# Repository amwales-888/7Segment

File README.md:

# 7Segment
Simple Large 7Segment Display

Who doesn't love big 7Segment displays?
Modelled the hardware in solidworks, printed on BambuLabs P1S. PCBs designed in KiCAD and boards manufactured by JLPCB.
The microcontroller I am using is a dsPIC33CK and it is interfaced to the WS2812 chips through DMA->SPI. It took quite a bit of fiddling to get the DMA->SPI working. 
</p>
For the clock I used a battery backed ds3102, 3 button's allow you to set the time and change the colors.
</p>
<table>
  <tr>
    <td> </td>
    <td> </td>
  </tr>
  <tr>
    <td> </td>
    <td> </td>
  </tr>
  <tr>
    <td> </td>
    <td> </td>
  </tr>
</table>

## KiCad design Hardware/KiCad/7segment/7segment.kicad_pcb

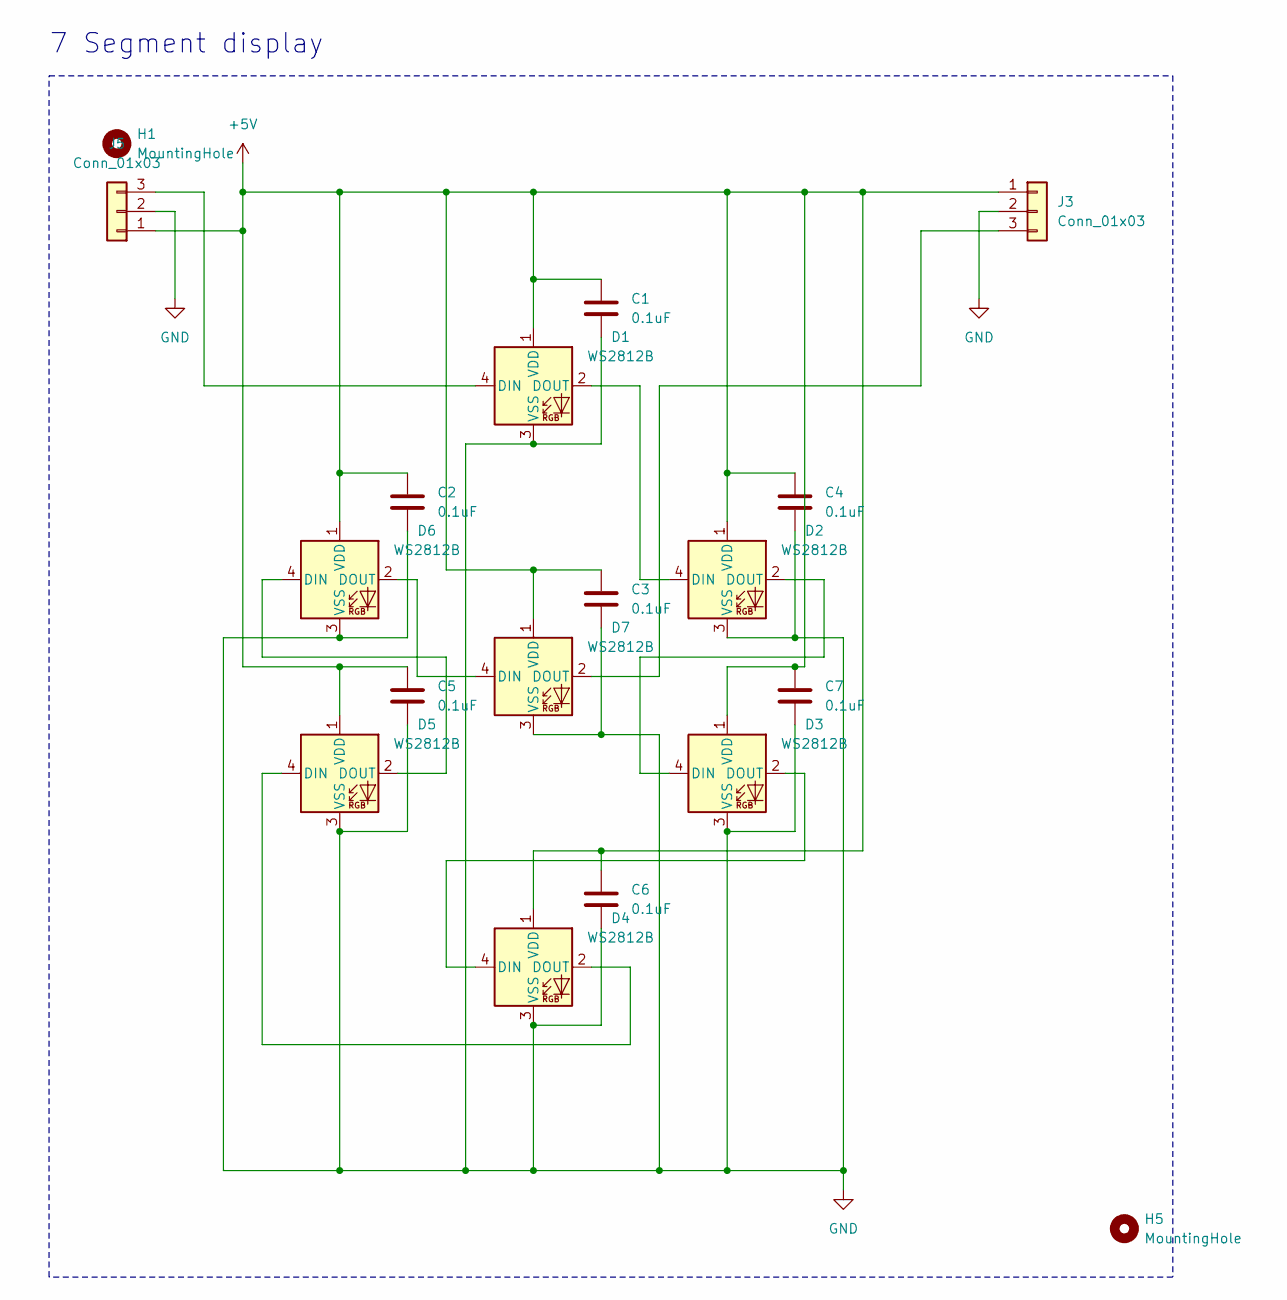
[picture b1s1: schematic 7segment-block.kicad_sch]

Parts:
C1, C2, C3, C4, C5, C6, C7: 0.1uF; C_0805_2012Metric_Pad1.18x1.45mm_HandSolder
D1, D2, D3, D4, D5, D6, D7: WS2812B; LED_WS2812B_PLCC4_5.0x5.0mm_P3.2mm
H1, H5: MountingHole; MountingHole_3.2mm_M3
J3, J5: Conn_01x03; PinHeader_1x03_P2.54mm_Vertical

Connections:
+5V: C1.1, C2.1, C3.1, C4.1, C5.1, C6.1, C7.1, D1.1 (VDD), D2.1 (VDD), D3.1 (VDD), D4.1 (VDD), D5.1 (VDD), D6.1 (VDD), D7.1 (VDD), J3.1, J5.1
GND: C1.2, C2.2, C3.2, C4.2, C5.2, C6.2, C7.2, D1.3 (VSS), D2.3 (VSS), D3.3 (VSS), D4.3 (VSS), D5.3 (VSS), D6.3 (VSS), D7.3 (VSS), J3.2, J5.2
unnamed: D1.4 (DIN), J5.3
unnamed: D1.2 (DOUT), D2.4 (DIN)
unnamed: D2.2 (DOUT), D3.4 (DIN)
unnamed: D3.2 (DOUT), D4.4 (DIN)
unnamed: D4.2 (DOUT), D5.4 (DIN)
unnamed: D5.2 (DOUT), D6.4 (DIN)
unnamed: D6.2 (DOUT), D7.4 (DIN)
unnamed: D7.2 (DOUT), J3.3

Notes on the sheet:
7 Segment display

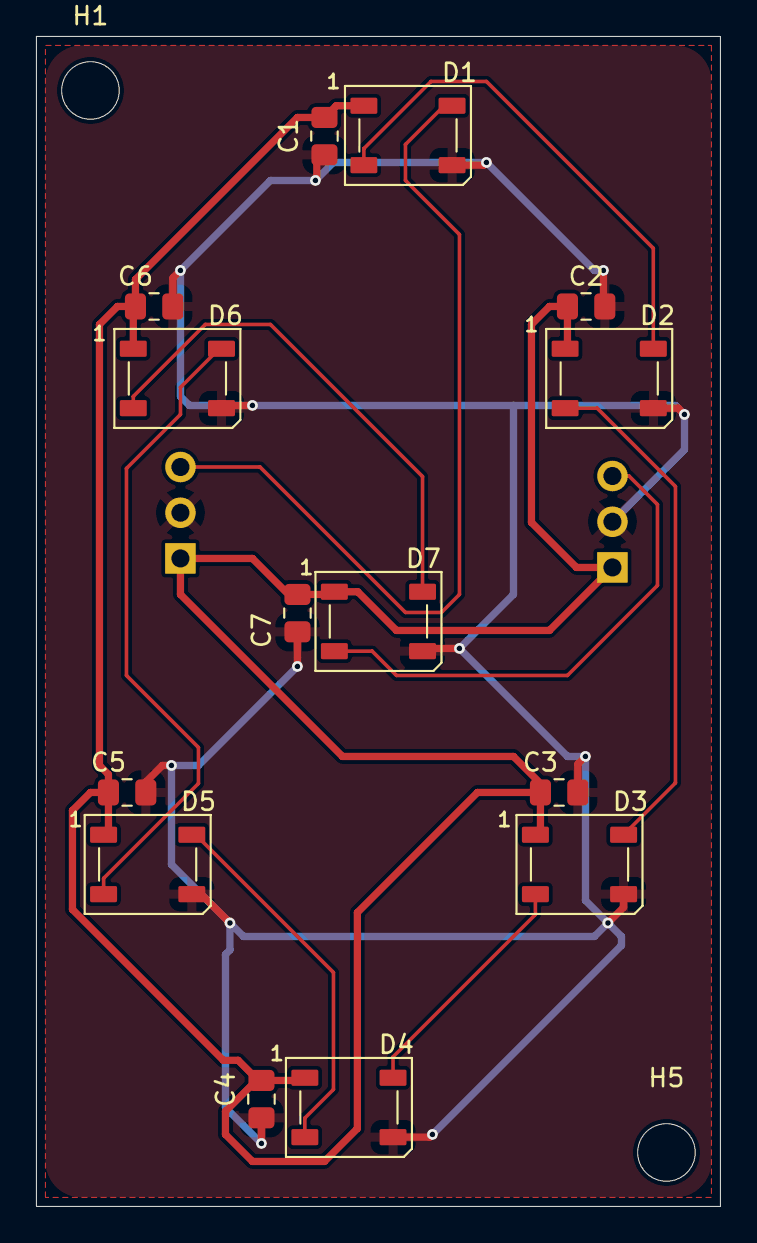
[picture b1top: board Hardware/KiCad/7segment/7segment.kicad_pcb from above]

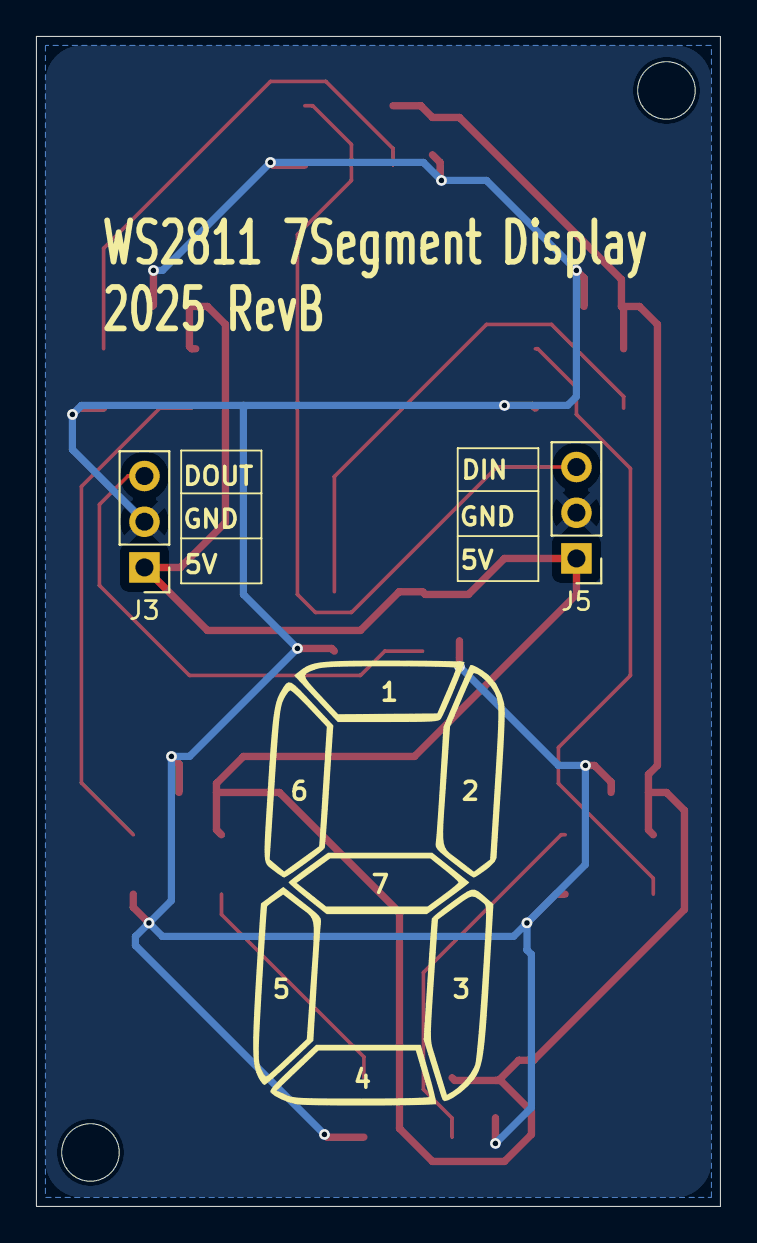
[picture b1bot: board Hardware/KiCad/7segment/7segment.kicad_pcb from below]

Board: 2 copper layers, 38.0 x 65.0 mm, 18 parts (2 on the bottom side), 10 nets.

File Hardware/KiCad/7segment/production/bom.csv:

Designator,Footprint,Quantity,Value,LCSC Part #
"C1, C2, C3, C4, C5, C6, C7",0805,7,0.1uF,
"D1, D2, D3, D4, D5, D6, D7",LED_WS2812B_PLCC4_5.0x5.0mm_P3.2mm,7,WS2812B,
"J3, J5",PinHeader_1x03_P2.54mm_Vertical,2,Conn_01x03,

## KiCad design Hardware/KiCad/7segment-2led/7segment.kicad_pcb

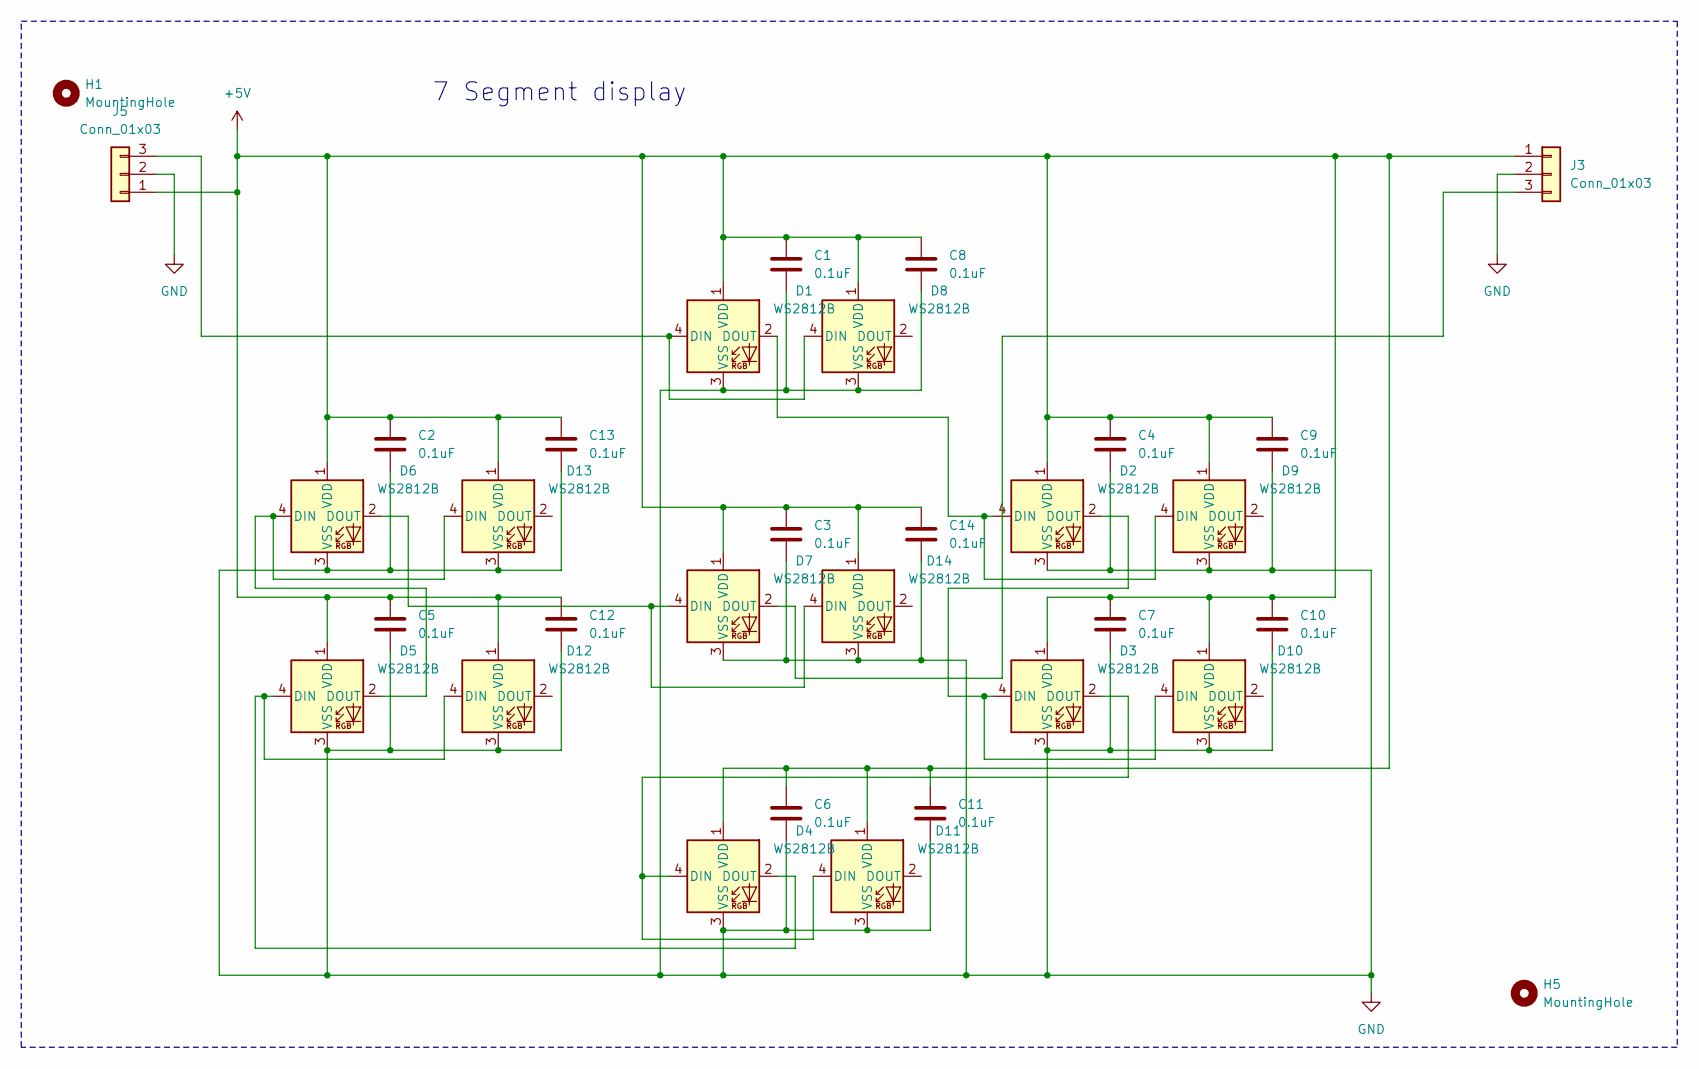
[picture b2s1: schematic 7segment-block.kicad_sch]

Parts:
C1, C2, C3, C4, C5, C6, C7, C8, C9, C10, C11, C12, C13, C14: 0.1uF; C_0805_2012Metric_Pad1.18x1.45mm_HandSolder
D1, D2, D3, D4, D5, D6, D7, D8, D9, D10, D11, D12, D13, D14: WS2812B; LED_WS2812B_PLCC4_5.0x5.0mm_P3.2mm
H1, H5: MountingHole; MountingHole_3.2mm_M3
J3, J5: Conn_01x03; PinHeader_1x03_P2.54mm_Vertical

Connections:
+5V: C1.1, C2.1, C3.1, C4.1, C5.1, C6.1, C7.1, C8.1, C9.1, C10.1, C11.1, C12.1, C13.1, C14.1, D1.1 (VDD), D2.1 (VDD), D3.1 (VDD), D4.1 (VDD), D5.1 (VDD), D6.1 (VDD), D7.1 (VDD), D8.1 (VDD), D9.1 (VDD), D10.1 (VDD), D11.1 (VDD), D12.1 (VDD), D13.1 (VDD), D14.1 (VDD), J3.1, J5.1
GND: C1.2, C2.2, C3.2, C4.2, C5.2, C6.2, C7.2, C8.2, C9.2, C10.2, C11.2, C12.2, C13.2, C14.2, D1.3 (VSS), D2.3 (VSS), D3.3 (VSS), D4.3 (VSS), D5.3 (VSS), D6.3 (VSS), D7.3 (VSS), D8.3 (VSS), D9.3 (VSS), D10.3 (VSS), D11.3 (VSS), D12.3 (VSS), D13.3 (VSS), D14.3 (VSS), J3.2, J5.2
unnamed: D1.4 (DIN), D8.4 (DIN), J5.3
unnamed: D1.2 (DOUT), D2.4 (DIN), D9.4 (DIN)
unnamed: D7.2 (DOUT), J3.3
unnamed: D2.2 (DOUT), D3.4 (DIN), D10.4 (DIN)
unnamed: D3.2 (DOUT), D4.4 (DIN), D11.4 (DIN)
unnamed: D4.2 (DOUT), D5.4 (DIN), D12.4 (DIN)
unnamed: D5.2 (DOUT), D6.4 (DIN), D13.4 (DIN)
unnamed: D6.2 (DOUT), D7.4 (DIN), D14.4 (DIN)

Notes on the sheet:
7 Segment display

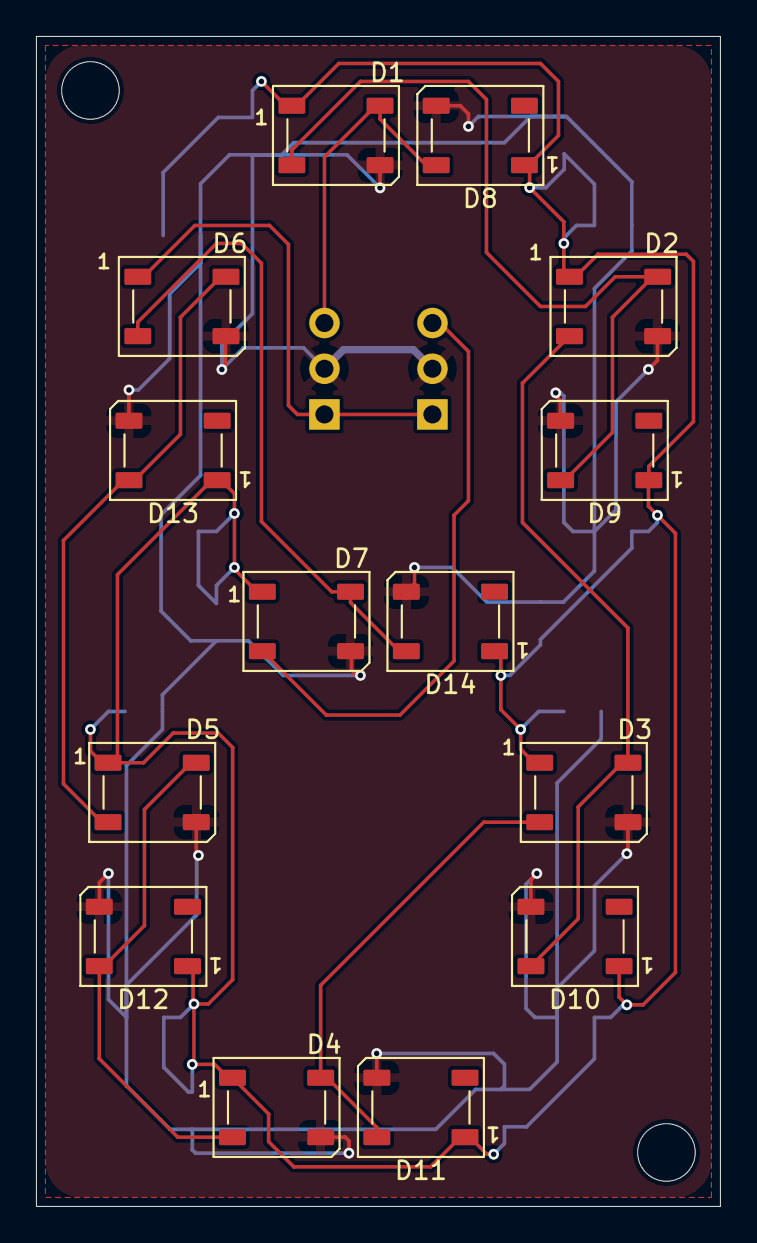
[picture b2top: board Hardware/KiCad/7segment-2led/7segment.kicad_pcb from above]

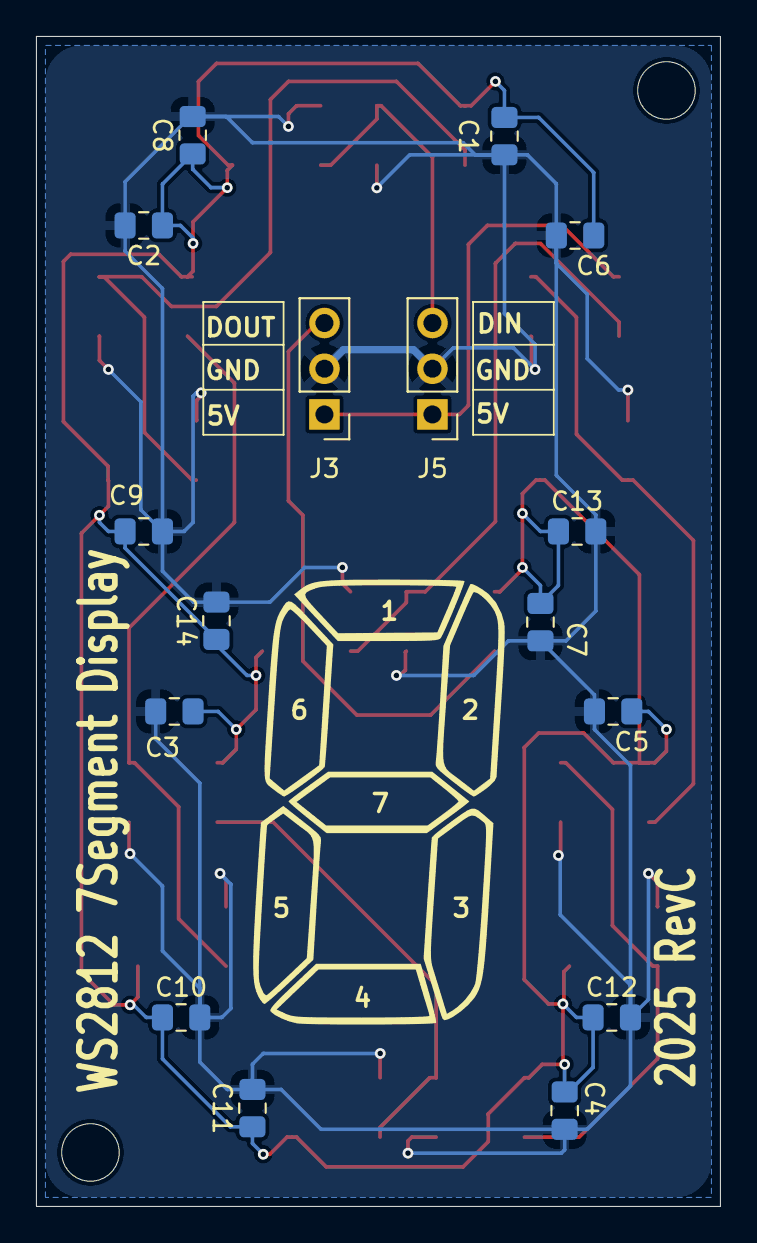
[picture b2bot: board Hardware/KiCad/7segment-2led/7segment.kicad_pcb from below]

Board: 2 copper layers, 38.0 x 65.0 mm, 32 parts (16 on the bottom side), 10 nets.

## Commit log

2025-11-23 Initial checkin
    WS2812 7Segment display
2025-11-23 Add Images
2025-11-23 Add Demo
    Simple 7Segment led pattern increments from 0-9
2025-11-25 Fix SPI/DMA Issue
    Looks like the SPI would stall around 30bits, I replaced the count with 1 on the dma channel continuously reading from the SPI buffer and this fixed it.
2025-11-25 Clean up and remove unecessary code from MCC
2025-11-26 Add docs for WS2812B
2025-11-26 Add license and change period to 300ns from 340ns to fit specs in Datasheet
2025-11-26 Add image
2025-12-01 Refactored code added ds1302 rttc support and made simple 4-7segment clock
2025-12-06 Working clock implementation
    Can now set the time with 3 buttons, hold the set button for 3-4 seconds, other buttons +- step through hours, minutes, blinks while setting
2025-12-06 Move DMS->SPI info about ws2812 to DMASPI file
2025-12-06 Named constant for SEGMENTVALUEOFF
2025-12-08 Swapped MSB and LSB when outputting to ws2812
2025-12-08 rename documentation to make it easier to find
2025-12-09 Added change color feature and fixed bug with missing write protect enable/disable when starting clock
2025-12-09 forgot to commit changes for enable/disable write protect
2025-12-10 Added image of clock
